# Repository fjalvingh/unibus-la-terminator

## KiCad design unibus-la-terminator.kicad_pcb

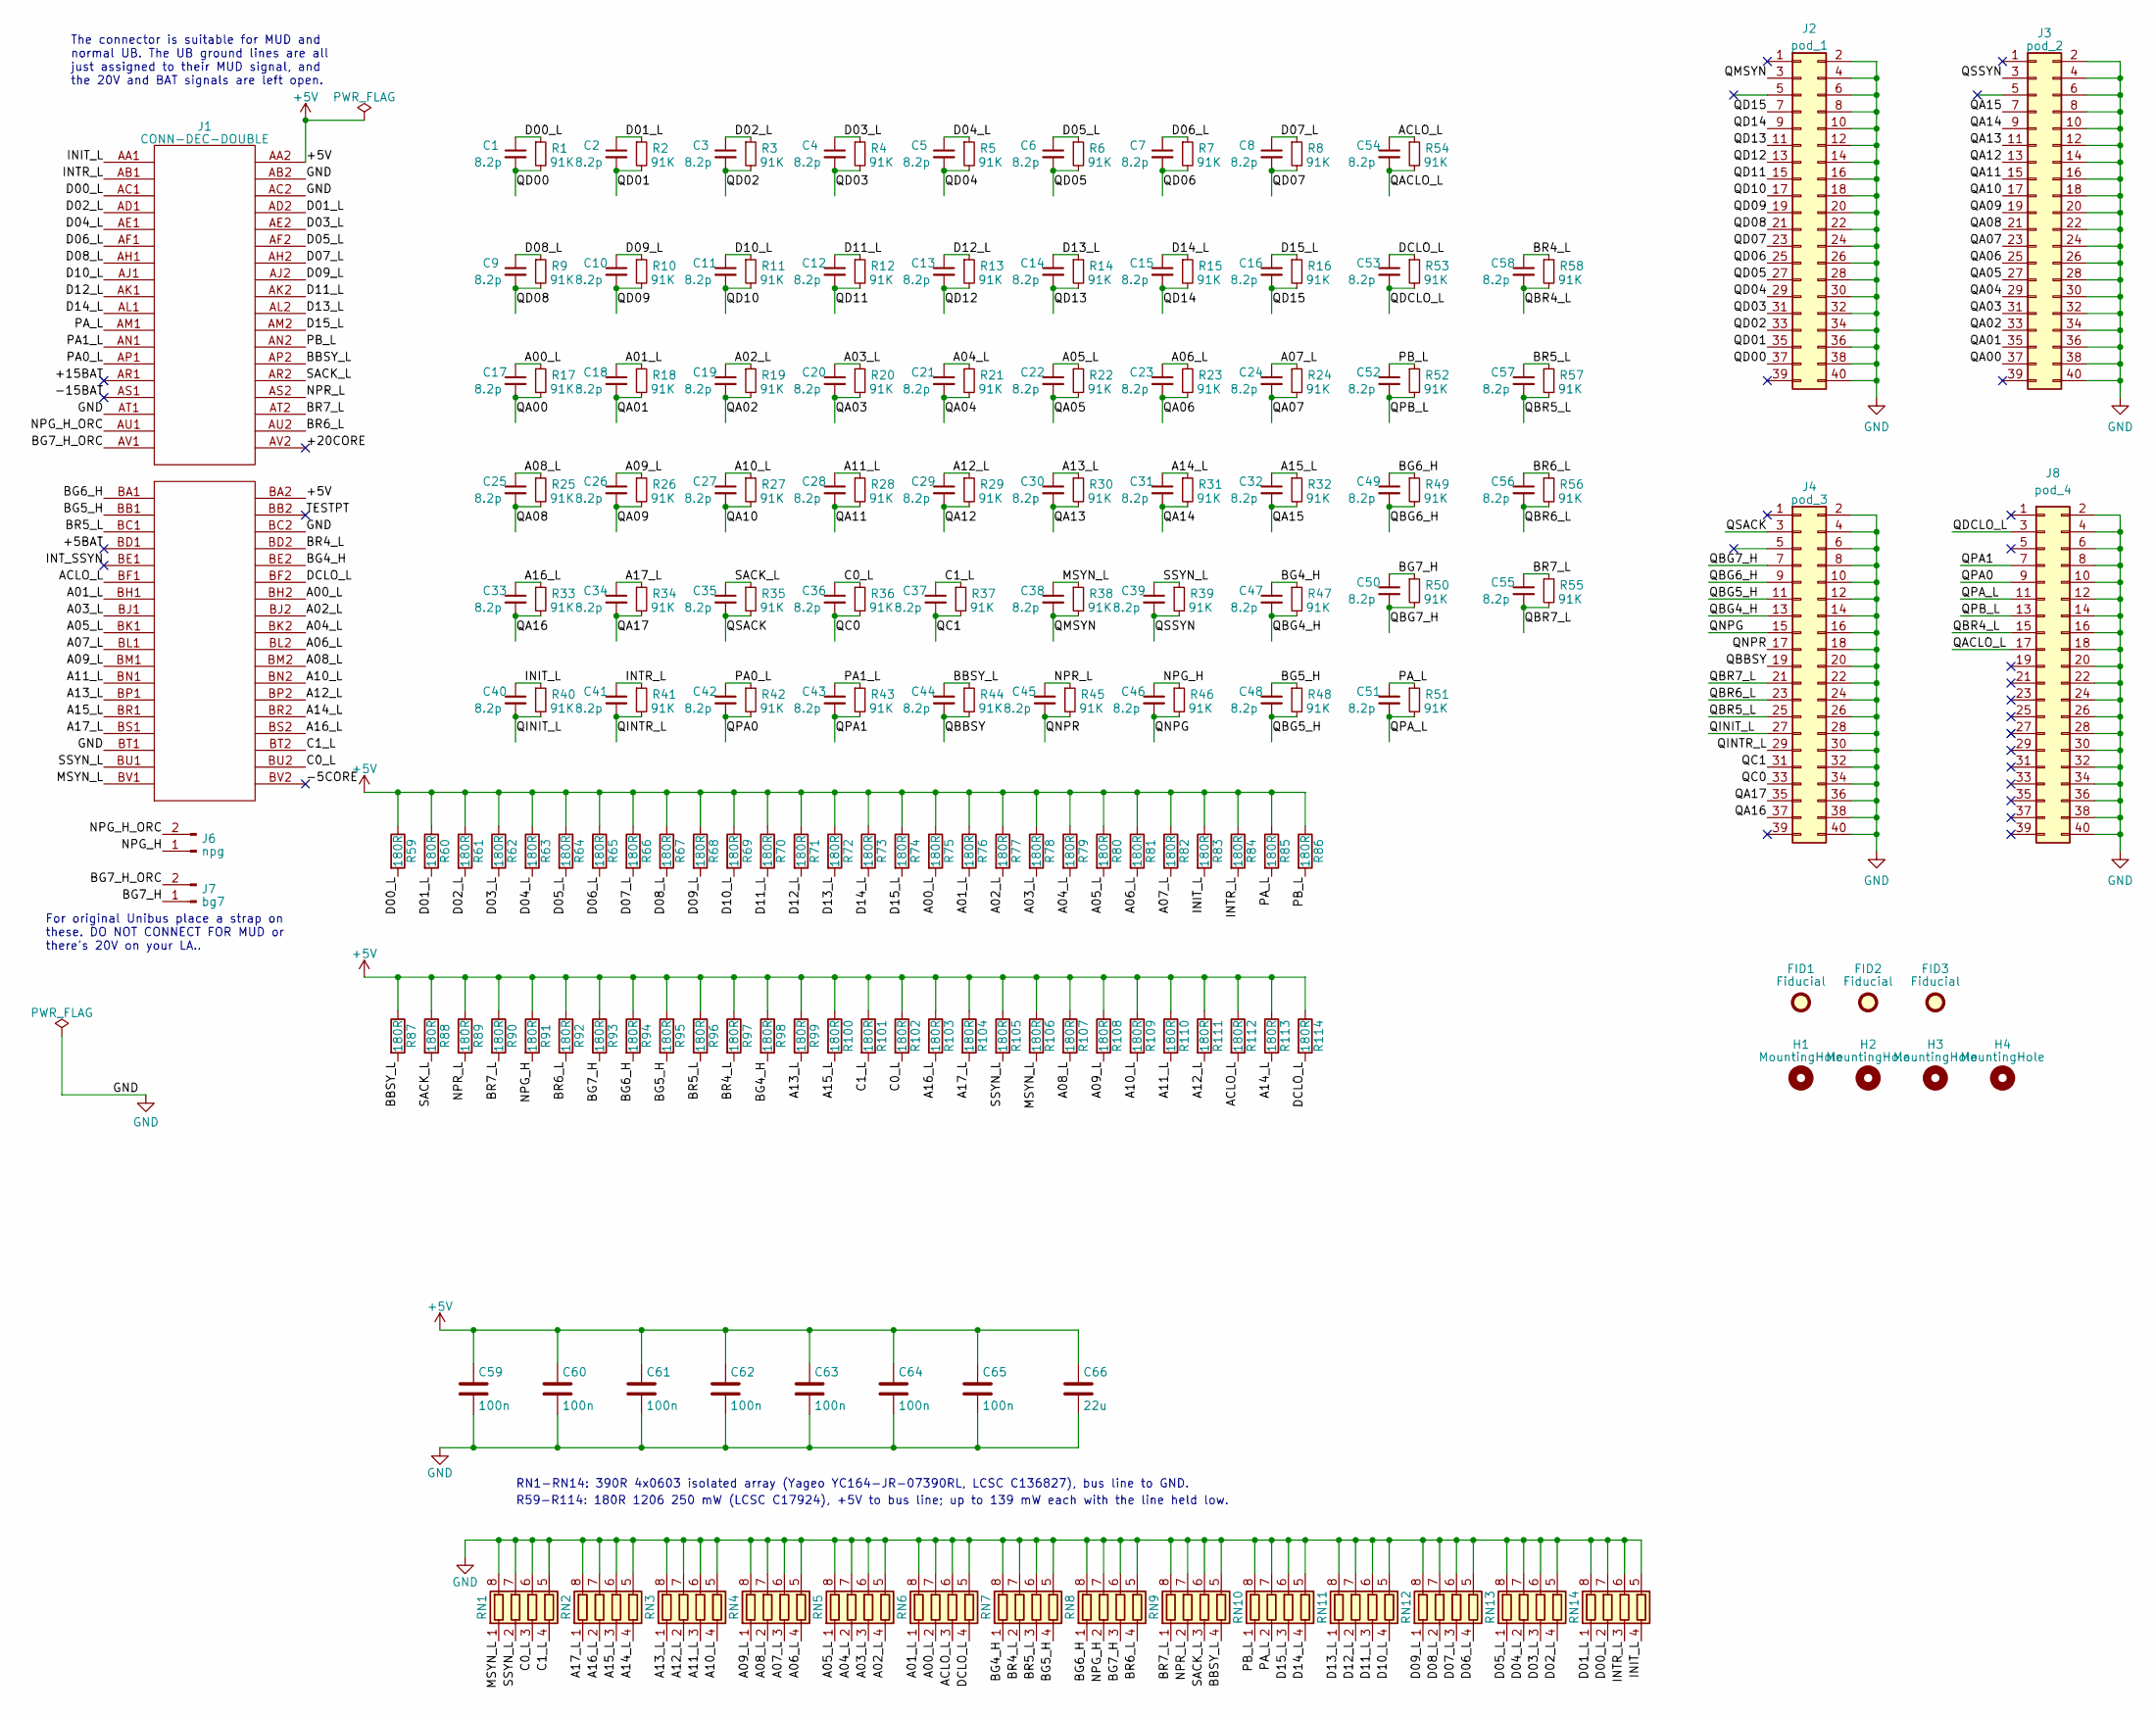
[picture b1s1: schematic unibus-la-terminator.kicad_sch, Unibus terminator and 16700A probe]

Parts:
C1, C2, C3, C4, C5, C6, C7, C8, C9, C10, C11, C12, C13, C14, C15, C16, C17, C18, C19, C20, C21, C22, C23, C24, C25, C26, C27, C28, C29, C30, C31, C32, C33, C34, C35, C36, C37, C38, C39, C40, C41, C42, C43, C44, C45, C46, C47, C48, C49, C50, C51, C52, C53, C54, C55, C56, C57, C58: 8.2p; C_0603_1608Metric_Pad1.08x0.95mm_HandSolder; LCSC C1685
C59, C60, C61, C62, C63, C64, C65: 100n; C_0603_1608Metric_Pad1.08x0.95mm_HandSolder; LCSC C14663
C66: 22u; C_1206_3216Metric_Pad1.33x1.80mm_HandSolder; LCSC C12891
FID1, FID2, FID3: Fiducial; Fiducial_1mm_Mask2mm
H1, H2, H3, H4: MountingHole; MountingHole_3.2mm_M3
J1: CONN-DEC-DOUBLE
J2: pod_1; PinHeader_2x20_P2.54mm_Horizontal
J3: pod_2; PinHeader_2x20_P2.54mm_Horizontal
J4: pod_3; PinHeader_2x20_P2.54mm_Horizontal
J6: npg; PinHeader_1x02_P2.54mm_Vertical
J7: bg7; PinHeader_1x02_P2.54mm_Vertical
J8: pod_4; PinHeader_2x20_P2.54mm_Horizontal
R1, R2, R3, R4, R5, R6, R7, R8, R9, R10, R11, R12, R13, R14, R15, R16, R17, R18, R19, R20, R21, R22, R23, R24, R25, R26, R27, R28, R29, R30, R31, R32, R33, R34, R35, R36, R37, R38, R39, R40, R41, R42, R43, R44, R45, R46, R47, R48, R49, R50, R51, R52, R53, R54, R55, R56, R57, R58: 91K; R_0603_1608Metric_Pad0.98x0.95mm_HandSolder; LCSC C23265
R59, R60, R61, R62, R63, R64, R65, R66, R67, R68, R69, R70, R71, R72, R73, R74, R75, R76, R77, R78, R79, R80, R81, R82, R83, R84, R85, R86, R87, R88, R89, R90, R91, R92, R93, R94, R95, R96, R97, R98, R99, R100, R101, R102, R103, R104, R105, R106, R107, R108, R109, R110, R111, R112, R113, R114: 180R; R_1206_3216Metric_Pad1.30x1.75mm_HandSolder; LCSC C17924
RN1, RN2, RN3, RN4, RN5, RN6, RN7, RN8, RN9, RN10, RN11, RN12, RN13, RN14: 390R; R_Array_Convex_4x0603; LCSC C136827

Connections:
+5V: C59.1, C60.1, C61.1, C62.1, C63.1, C64.1, C65.1, C66.1, J1.AA2, J1.BA2, R59.1, R60.1, R61.1, R62.1, R63.1, R64.1, R65.1, R66.1, R67.1, R68.1, R69.1, R70.1, R71.1, R72.1, R73.1, R74.1, R75.1, R76.1, R77.1, R78.1, R79.1, R80.1, R81.1, R82.1, R83.1, R84.1, R85.1, R86.1, R87.1, R88.1, R89.1, R90.1, R91.1, R92.1, R93.1, R94.1, R95.1, R96.1, R97.1, R98.1, R99.1, R100.1, R101.1, R102.1, R103.1, R104.1, R105.1, R106.1, R107.1, R108.1, R109.1, R110.1, R111.1, R112.1, R113.1, R114.1
/+5BAT: J1.BD1
/+15BAT: J1.AR1
/+20CORE: J1.AV2
/-5CORE: J1.BV2
/-15BAT: J1.AS1
/A00_L: C17.1, J1.BH2, R17.1, R75.2, RN6.2 (R2.1)
/A01_L: C18.1, J1.BH1, R18.1, R76.2, RN6.1 (R1.1)
/A02_L: C19.1, J1.BJ2, R19.1, R77.2, RN5.4 (R4.1)
/A03_L: C20.1, J1.BJ1, R20.1, R78.2, RN5.3 (R3.1)
/A04_L: C21.1, J1.BK2, R21.1, R79.2, RN5.2 (R2.1)
/A05_L: C22.1, J1.BK1, R22.1, R80.2, RN5.1 (R1.1)
/A06_L: C23.1, J1.BL2, R23.1, R81.2, RN4.4 (R4.1)
/A07_L: C24.1, J1.BL1, R24.1, R82.2, RN4.3 (R3.1)
/A08_L: C25.1, J1.BM2, R25.1, R107.2, RN4.2 (R2.1)
/A09_L: C26.1, J1.BM1, R26.1, R108.2, RN4.1 (R1.1)
/A10_L: C27.1, J1.BN2, R27.1, R109.2, RN3.4 (R4.1)
/A11_L: C28.1, J1.BN1, R28.1, R110.2, RN3.3 (R3.1)
/A12_L: C29.1, J1.BP2, R29.1, R111.2, RN3.2 (R2.1)
/A13_L: C30.1, J1.BP1, R30.1, R99.2, RN3.1 (R1.1)
/A14_L: C31.1, J1.BR2, R31.1, R113.2, RN2.4 (R4.1)
/A15_L: C32.1, J1.BR1, R32.1, R100.2, RN2.3 (R3.1)
/A16_L: C33.1, J1.BS2, R33.1, R103.2, RN2.2 (R2.1)
/A17_L: C34.1, J1.BS1, R34.1, R104.2, RN2.1 (R1.1)
/ACLO_L: C54.1, J1.BF1, R54.1, R112.2, RN6.3 (R3.1)
/BBSY_L: C44.1, J1.AP2, R44.1, R87.2, RN9.4 (R4.1)
/BG4_H: C47.1, J1.BE2, R47.1, R98.2, RN7.1 (R1.1)
/BG5_H: C48.1, J1.BB1, R48.1, R95.2, RN7.4 (R4.1)
/BG6_H: C49.1, J1.BA1, R49.1, R94.2, RN8.1 (R1.1)
/BG7_H: C50.1, J7.1, R50.1, R93.2, RN8.3 (R3.1)
/BG7_H_ORC: J1.AV1, J7.2
/BR4_L: C58.1, J1.BD2, R58.1, R97.2, RN7.2 (R2.1)
/BR5_L: C57.1, J1.BC1, R57.1, R96.2, RN7.3 (R3.1)
/BR6_L: C56.1, J1.AU2, R56.1, R92.2, RN8.4 (R4.1)
/BR7_L: C55.1, J1.AT2, R55.1, R90.2, RN9.1 (R1.1)
/C0_L: C36.1, J1.BU2, R36.1, R102.2, RN1.3 (R3.1)
/C1_L: C37.1, J1.BT2, R37.1, R101.2, RN1.4 (R4.1)
/D00_L: C1.1, J1.AC1, R1.1, R59.2, RN14.2 (R2.1)
/D01_L: C2.1, J1.AD2, R2.1, R60.2, RN14.1 (R1.1)
/D02_L: C3.1, J1.AD1, R3.1, R61.2, RN13.4 (R4.1)
/D03_L: C4.1, J1.AE2, R4.1, R62.2, RN13.3 (R3.1)
/D04_L: C5.1, J1.AE1, R5.1, R63.2, RN13.2 (R2.1)
/D05_L: C6.1, J1.AF2, R6.1, R64.2, RN13.1 (R1.1)
/D06_L: C7.1, J1.AF1, R7.1, R65.2, RN12.4 (R4.1)
/D07_L: C8.1, J1.AH2, R8.1, R66.2, RN12.3 (R3.1)
/D08_L: C9.1, J1.AH1, R9.1, R67.2, RN12.2 (R2.1)
/D09_L: C10.1, J1.AJ2, R10.1, R68.2, RN12.1 (R1.1)
/D10_L: C11.1, J1.AJ1, R11.1, R69.2, RN11.4 (R4.1)
/D11_L: C12.1, J1.AK2, R12.1, R70.2, RN11.3 (R3.1)
/D12_L: C13.1, J1.AK1, R13.1, R71.2, RN11.2 (R2.1)
/D13_L: C14.1, J1.AL2, R14.1, R72.2, RN11.1 (R1.1)
/D14_L: C15.1, J1.AL1, R15.1, R73.2, RN10.4 (R4.1)
/D15_L: C16.1, J1.AM2, R16.1, R74.2, RN10.3 (R3.1)
/DCLO_L: C53.1, J1.BF2, R53.1, R114.2, RN6.4 (R4.1)
/INIT_L: C40.1, J1.AA1, R40.1, R83.2, RN14.4 (R4.1)
/INTR_L: C41.1, J1.AB1, R41.1, R84.2, RN14.3 (R3.1)
/INT_SSYN: J1.BE1
/MSYN_L: C38.1, J1.BV1, R38.1, R106.2, RN1.1 (R1.1)
/NPG_H: C46.1, J6.1, R46.1, R91.2, RN8.2 (R2.1)
/NPG_H_ORC: J1.AU1, J6.2
/NPR_L: C45.1, J1.AS2, R45.1, R89.2, RN9.2 (R2.1)
/PA0_L: C42.1, J1.AP1, R42.1
/PA1_L: C43.1, J1.AN1, R43.1
/PA_L: C51.1, J1.AM1, R51.1, R85.2, RN10.2 (R2.1)
/PB_L: C52.1, J1.AN2, R52.1, R86.2, RN10.1 (R1.1)
/QA00: C17.2, J3.37, R17.2
/QA01: C18.2, J3.35, R18.2
/QA02: C19.2, J3.33, R19.2
/QA03: C20.2, J3.31, R20.2
/QA04: C21.2, J3.29, R21.2
/QA05: C22.2, J3.27, R22.2
/QA06: C23.2, J3.25, R23.2
/QA07: C24.2, J3.23, R24.2
/QA08: C25.2, J3.21, R25.2
/QA09: C26.2, J3.19, R26.2
/QA10: C27.2, J3.17, R27.2
/QA11: C28.2, J3.15, R28.2
/QA12: C29.2, J3.13, R29.2
/QA13: C30.2, J3.11, R30.2
/QA14: C31.2, J3.9, R31.2
/QA15: C32.2, J3.7, R32.2
/QA16: C33.2, J4.37, R33.2
/QA17: C34.2, J4.35, R34.2
/QACLO_L: C54.2, J8.17, R54.2
/QBBSY: C44.2, J4.19, R44.2
/QBG4_H: C47.2, J4.13, R47.2
/QBG5_H: C48.2, J4.11, R48.2
/QBG6_H: C49.2, J4.9, R49.2
/QBG7_H: C50.2, J4.7, R50.2
/QBR4_L: C58.2, J8.15, R58.2
/QBR5_L: C57.2, J4.25, R57.2
/QBR6_L: C56.2, J4.23, R56.2
/QBR7_L: C55.2, J4.21, R55.2
/QC0: C36.2, J4.33, R36.2
/QC1: C37.2, J4.31, R37.2
/QD00: C1.2, J2.37, R1.2
/QD01: C2.2, J2.35, R2.2
/QD02: C3.2, J2.33, R3.2
/QD03: C4.2, J2.31, R4.2
/QD04: C5.2, J2.29, R5.2
/QD05: C6.2, J2.27, R6.2
/QD06: C7.2, J2.25, R7.2
/QD07: C8.2, J2.23, R8.2
/QD08: C9.2, J2.21, R9.2
/QD09: C10.2, J2.19, R10.2
/QD10: C11.2, J2.17, R11.2
/QD11: C12.2, J2.15, R12.2
/QD12: C13.2, J2.13, R13.2
/QD13: C14.2, J2.11, R14.2
/QD14: C15.2, J2.9, R15.2
/QD15: C16.2, J2.7, R16.2
/QDCLO_L: C53.2, J8.3, R53.2
/QINIT_L: C40.2, J4.27, R40.2
/QINTR_L: C41.2, J4.29, R41.2
/QMSYN: C38.2, J2.3, R38.2
/QNPG: C46.2, J4.15, R46.2
/QNPR: C45.2, J4.17, R45.2
/QPA0: C42.2, J8.9, R42.2
/QPA1: C43.2, J8.7, R43.2
/QPA_L: C51.2, J8.11, R51.2
/QPB_L: C52.2, J8.13, R52.2
/QSACK: C35.2, J4.3, R35.2
/QSSYN: C39.2, J3.3, R39.2
/SACK_L: C35.1, J1.AR2, R35.1, R88.2, RN9.3 (R3.1)
/SSYN_L: C39.1, J1.BU1, R39.1, R105.2, RN1.2 (R2.1)
/TESTPT: J1.BB2
GND: C59.2, C60.2, C61.2, C62.2, C63.2, C64.2, C65.2, C66.2, J1.AB2, J1.AC2, J1.AT1, J1.BC2, J1.BT1, J2.2, J2.4, J2.6, J2.8, J2.10, J2.12, J2.14, J2.16, J2.18, J2.20, J2.22, J2.24, J2.26, J2.28, J2.30, J2.32, J2.34, J2.36, J2.38, J2.40, J3.2, J3.4, J3.6, J3.8, J3.10, J3.12, J3.14, J3.16, J3.18, J3.20, J3.22, J3.24, J3.26, J3.28, J3.30, J3.32, J3.34, J3.36, J3.38, J3.40, J4.2, J4.4, J4.6, J4.8, J4.10, J4.12, J4.14, J4.16, J4.18, J4.20, J4.22, J4.24, J4.26, J4.28, J4.30, J4.32, J4.34, J4.36, J4.38, J4.40, J8.2, J8.4, J8.6, J8.8, J8.10, J8.12, J8.14, J8.16, J8.18, J8.20, J8.22, J8.24, J8.26, J8.28, J8.30, J8.32, J8.34, J8.36, J8.38, J8.40, RN1.5 (R4.2), RN1.6 (R3.2), RN1.7 (R2.2), RN1.8 (R1.2), RN2.5 (R4.2), RN2.6 (R3.2), RN2.7 (R2.2), RN2.8 (R1.2), RN3.5 (R4.2), RN3.6 (R3.2), RN3.7 (R2.2), RN3.8 (R1.2), RN4.5 (R4.2), RN4.6 (R3.2), RN4.7 (R2.2), RN4.8 (R1.2), RN5.5 (R4.2), RN5.6 (R3.2), RN5.7 (R2.2), RN5.8 (R1.2), RN6.5 (R4.2), RN6.6 (R3.2), RN6.7 (R2.2), RN6.8 (R1.2), RN7.5 (R4.2), RN7.6 (R3.2), RN7.7 (R2.2), RN7.8 (R1.2), RN8.5 (R4.2), RN8.6 (R3.2), RN8.7 (R2.2), RN8.8 (R1.2), RN9.5 (R4.2), RN9.6 (R3.2), RN9.7 (R2.2), RN9.8 (R1.2), RN10.5 (R4.2), RN10.6 (R3.2), RN10.7 (R2.2), RN10.8 (R1.2), RN11.5 (R4.2), RN11.6 (R3.2), RN11.7 (R2.2), RN11.8 (R1.2), RN12.5 (R4.2), RN12.6 (R3.2), RN12.7 (R2.2), RN12.8 (R1.2), RN13.5 (R4.2), RN13.6 (R3.2), RN13.7 (R2.2), RN13.8 (R1.2), RN14.5 (R4.2), RN14.6 (R3.2), RN14.7 (R2.2), RN14.8 (R1.2)

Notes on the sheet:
RN1-RN14: 390R 4x0603 isolated array (Yageo YC164-JR-07390RL, LCSC C136827), bus line to GND.
R59-R114: 180R 1206 250 mW (LCSC C17924), +5V to bus line; up to 139 mW each with the line held low.
The connector is suitable for MUD and normal UB. The UB ground lines are all just assigned to their MUD signal, and the 20V and BAT signals are left open.
For original Unibus place a strap on these. DO NOT CONNECT FOR MUD or there's 20V on your LA..

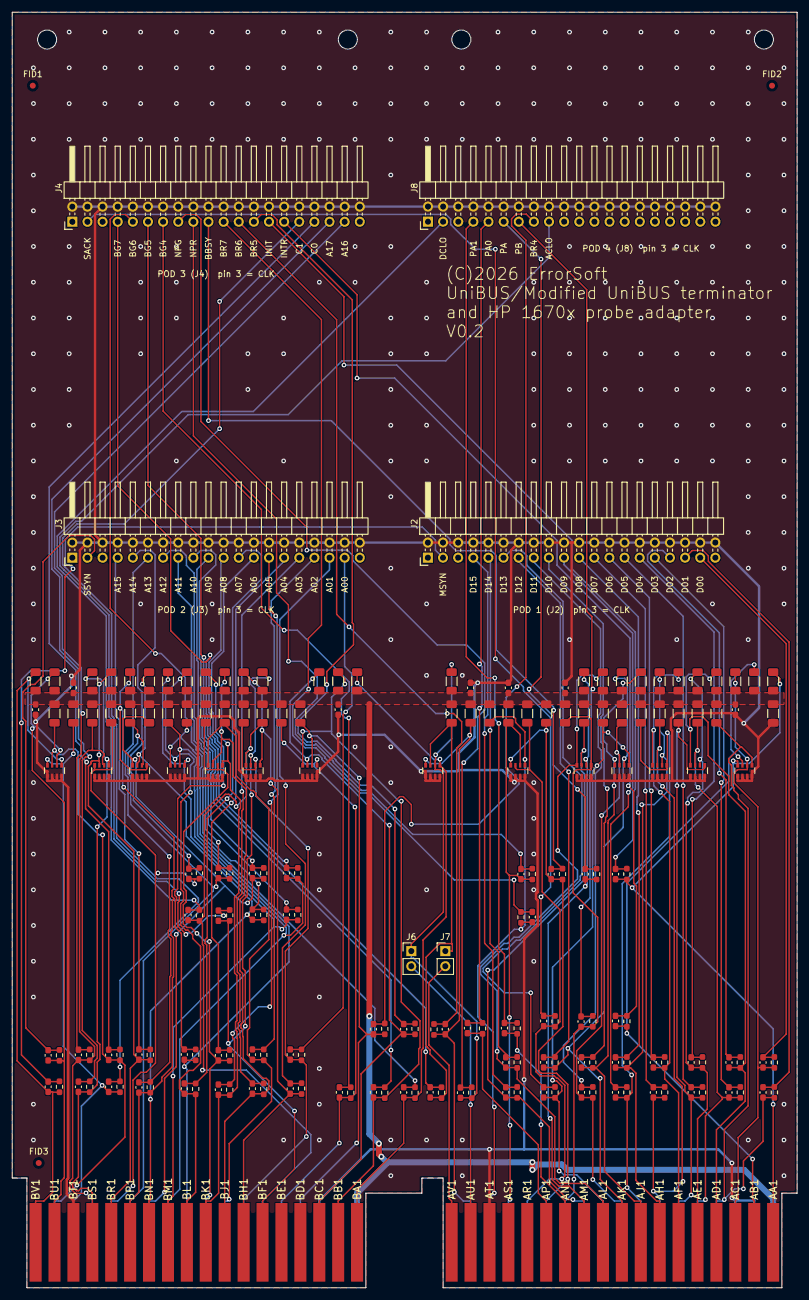
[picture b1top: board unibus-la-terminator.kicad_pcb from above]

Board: 2 copper layers, 131.7 x 214.1 mm, 208 parts (0 on the bottom side), 120 nets.

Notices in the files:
unibus-la-terminator.kicad_pcb:
(C)2026 ErrorSoft
